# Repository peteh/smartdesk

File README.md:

# HOMEASSISTANT SMART DESK CONTROL FOR ASSMANN TABLES

This project aims to control Assmann desks via Homeassistant.

## Compatibility

The following desks have been confirmed working:

* Assmann Easy <https://www.assmann.de/produkt/easy/>

## Credits

myDeskControl Steuerung - initial idea how to control the desk

<https://github.com/moesterheld/deskcontrol>

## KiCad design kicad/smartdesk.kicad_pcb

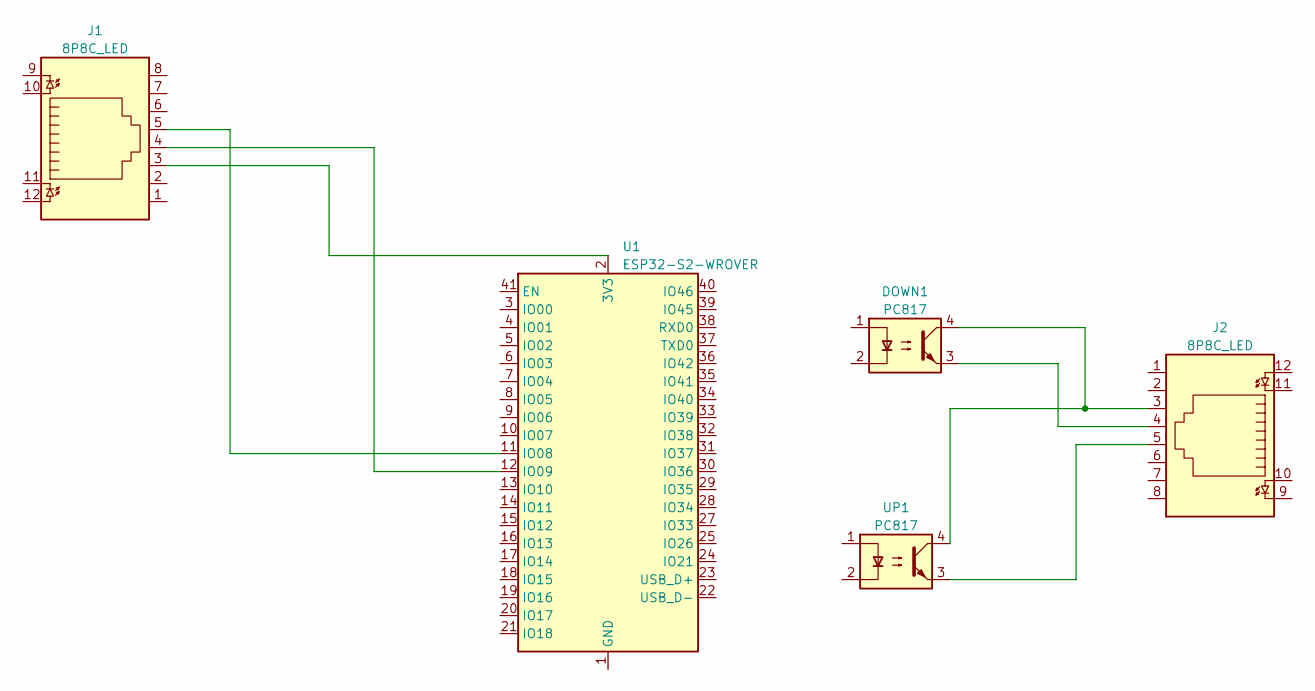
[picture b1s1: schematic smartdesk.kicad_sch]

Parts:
DOWN1: PC817; DIP-4_W7.62mm
J1, J2: 8P8C_LED; RJ45_Amphenol_RJHSE538X
U1: ESP32-S2-WROVER
UP1: PC817; DIP-4_W7.62mm

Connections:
unnamed: DOWN1.3, J2.4
unnamed: DOWN1.4, J2.3, UP1.4
unnamed: J2.5, UP1.3
unnamed: J1.3, U1.2 (3V3)
unnamed: U1.1 (GND), U1.26 (GND), U1.42 (GND), U1.43 (GND)
unnamed: J1.5, U1.11 (IO08)
unnamed: J1.4, U1.12 (IO09)

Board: 2 copper layers, 5 parts (0 on the bottom side), 7 nets, no tracks yet.

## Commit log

2023-03-19 ADD: inital commit
2023-03-19 ADD: desk class
2023-03-19 ADD: presets
2023-03-19 ADD: preset calculation
2023-03-19 ADD: icons and some enum fixes
2023-05-04 ADD: infrared distance sensor, state update
2023-05-05 CHG: refactor preset code
2023-05-25 ADD: more generalization and lower and upper limit
2023-05-26 ADD: first draft kicad
